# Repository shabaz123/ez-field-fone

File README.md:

# E-Z Field Fone

This repository contains a project for an intercom / field phone. The design uses discrete components throughout.  

The design includes:
- KiCad 10 Schematic and PCB files
- KiCad 10 SPICE Simulation Workbook
- Gerber files for fabrication  
- PDF schematic export and PCB screenshots for easy viewing without KiCad

# How It Works

The audio input (from on-board mic, or via a handset/earpiece jack socket) is amplified, then sent over bell wire to the remote unit. The signal on the bell wire is fed into a difference amplifier, in order to subtract the local audio. The difference output is fed into a power amplifier. The user can signal a call alert by applying a DC voltage onto the bell wire. There is an amplifier that is sensitive to DC, and the output can be used to light an indicator or sound a buzzer alert.

# Printed Circuit Board Overview

The design is split up into two separate printed circuit boards (PCBs). One PCB contains the microphone amplifier (Mic Booard) and the other contains everything else (Main Board). You'll need a mic board, and a main board, for each unit. The two boards are designed to fit into at least a couple of different enclosures. 

# Enclosures

The circuit boards will comfortably fit inside a Hammond 1559E enclosure (170 x 85 x 34 mm) along with a large 60 mm diameter (66 x 66 mm square) 8 ohm speaker such as Pui AS06608PS-R and a PP3 battery. 

If you prefer to omit the speaker and use an external handset, then a smaller Hammond 1593X (140 x 66 x 28 mm) can be used. 

If you wish to use any other enclosure, the PCB dimensions are:

Mic Board: 59 x 32.5 mm

Main Board: 59 x 55 mm

# Mic Board

The mic board uses a preamplifier designed by M. Kellett.

- **Gain:** ~45 dB  
- **Bandwidth (-3 dB):** ~100 Hz to 7 kHz (approximate)

## Schematic

## Board Connections

Two sets of soldered connections need to be made to the Mic Board; the microphone element, and the speaker. Also, an 8-pin connector is used to attach the Mic Board to the Main Board.

### Electret Mic Element

The Mic Board has a 2-pin location for soldering an electret mic element using screened cable

### Speaker

There is a 2-pin location for soldering an 8-ohm speaker

### Interfacing Connector

An 8-pin connector is used to connect a cable between the Mic Board and the Main Board. 

A ready-made JST PH 8-way "opposite direction", also known as "reverse direction" cable can be used (available from AliExpress). The opposite/reverse direction means that when laid flat, opposite sides of the connector are seen from one end to the other (this means that pin 1 of the both connectors are attached to each other, and pin 2 of both connectors are attached to each other, and so on; in contrast, a "same direction" cable has pin 1 on one connector wired to pin 8 of the other connector, and pin 2 to pin 7, and so on). 

Double-check you have the correct cable; do NOT purchase a "same direction" cable!

If you're using the larger Hammond enclosure, the cable length needs to ideally be 15cm (available from a few AliExpress stores) or alternatively 20cm (which more AliExpress stores offer). 

If you're using the smaller Hammond enclosure, a 10cm length cable should reach, but you'll need to measure it or try it out.

## 3.5 mm Audio Jack Pinout

If you wish to plug in an external mic and speaker/eaerphone, use the 3.5 mm 3-pin socket. Connections are:

- Tip: Audio Out, connect this to any earphone or headphones, or to an 8-ohm speaker
- Ring: Microphone, connect this to an electret mic element (the Mic Board PCB supplies a low voltage to power the element)
- Shield: Ground

## PCB Top

## PCB Underside

Note that one wire link needs to be made on the underside; it is labeled on the board.

## PCB Render

## Enclosure Cutouts

The Mic Board requires the following holes to be drilled in the enclosure:

- DC barrel socket
- Rotary switch (4-position, for Off/Standby/On/Call)
- Power ON LED indicator
- 3.5 mm audio socket (for external mic and external earphone/speaker)
- Hole for electret mic element

---

# Main Board

The main board includes a 280mW audio amplifier designed by M. Kellett. 

## Schematic

Note: Resistor R35 is specified to be 630 ohm, this is a hard-to-find value, it may be replaced by 620 ohm in series with 10 ohm (on the PCB, solder 620 ohm and 10 ohm vertically, and connect them at the top with solder).

## Board Connections

The only off-board connection from the Main Board is the 8-way connection that interfaces to the Mic Board. See the Mic Board notes earlier, for an explanation of the required cable (8-way JST PH cable, "opposite/reverse direction", i.e. identical pin mapping, pin 1 to pin 1, and pin 2 to pin 2, and so on).

## PCB Top

## PCB Underside

Note that there are two wire links that need to be soldered on the board underside. The connections are labeled A and B on the circuit board (connect A to A, and connect B to B).

## PCB Render

## Enclosure Cutouts

The Main Board requires the following holes to be drilled in the enclosure:

- An approximately 9 x 7.5 mm rectangular hole for a 3.81 mm pitch 2-way plug-in terminal block, used for attaching bell wire
- Two approximately 6 mm diameter holes, one for the mute button, and one for the recessed line termination button (the bell wire needs terminating at one end)
- 7.5 mm dia hole for the volume control potentiometer
- Hole for the call alert LED indicator
- Hole for an audio buzzer (if a buzzer is fitted) for audible call alerts

---

## Notes

All components are easy to source. 

For the input power, use a 9V PP3 battery, or use the 9V DC barrel socket (center positive).

The potentiometer can be ALPS RK097 series (available from AliExpress), it has pins at 2.5 mm pitch, and a body width of 10 mm.

The rotary switch is type RS1010 4-way (available from AliExpress)

The push switches can be either PS-12E05, or PN12 series by CK/Littelfuse

For the trimmer resistor, RM065 series will fit the PCB

The line connector (for attaching the bell wire) is a 2-way 3.81 mm pitch terminal block, there are many generic options. One example is WJ15EDGRC-3.81-02P-14-00A (which mates with part code WJ15EDGK-3.81-02P-14-00A

---

# Parts Lists

## Mic Board Parts List

| Reference  | Qty | Value             | Description                             |
| ---------- | --- | ----------------- | --------------------------------------- |
| C1         | 1   | 47u               | Electrolytic Capacitor 5mm dia          |
| C2,C3,C5   | 3   | 22u               | Electrolytic Capacitor 5mm dia          |
| C4         | 1   | 100n              | Ceramic Capacitor 5mm pitch             |
| C6         | 1   | 220p              | Ceramic Capacitor 5mm pitch             |
| C7         | 1   | 2.2n              | Ceramic Capacitor 5mm pitch             |
| D1         | 1   | 1N4148            | Small Signal Diode                      |
| D3         | 1   | LED_ON            | LED 3mm dia                             |
| J1         | 1   | ELECTRET_MIC      | Electret Mic Element                    |
| J2         | 1   | HANDSET           | SJ1-3525N 3.5mm jack CUI                |
| J3         | 1   | DC-Socket         | 2.1/5.5mm DC Jack Socket                |
| J4         | 1   | PP3 BATT          | Battery Clip PP3                        |
| J5         | 1   | SPEAKER           | AS06608PS-R 8-ohm  60mm dia (66 x 66mm) |
| J6         | 1   | B8B-PH-K-S        | JST PH Header 8-way Vertical            |
| Q1,Q3      | 2   | BC549             | NPN TO-92 Low Noise BJT                 |
| Q2         | 1   | BC559             | PNP TO-92 Low Noise BJT                 |
| Q4         | 1   | BC547             | NPN TO-92 BJT                           |
| Q5         | 1   | BS250P            | P-ch MOSFET TO-92                       |
| R1,R14,R17 | 3   | 1k                | Resistor 1/8W or 1/4W                   |
| R2         | 1   | 10k               | Resistor 1/8W or 1/4W                   |
| R3         | 1   | 91k               | Resistor 1/8W or 1/4W                   |
| R4         | 1   | 180k              | Resistor 1/8W or 1/4W                   |
| R5         | 1   | 56k               | Resistor 1/8W or 1/4W                   |
| R6         | 1   | 82R               | Resistor 1/8W or 1/4W                   |
| R7         | 1   | 560R              | Resistor 1/8W or 1/4W                   |
| R8         | 1   | 5.6k              | Resistor 1/8W or 1/4W                   |
| R9         | 1   | 2.7k              | Resistor 1/8W or 1/4W                   |
| R10        | 1   | 16k               | Resistor 1/8W or 1/4W                   |
| R11        | 1   | 4.7k              | Resistor 1/8W or 1/4W                   |
| R12,R13    | 2   | 3.9k              | Resistor 1/8W or 1/4W                   |
| R15        | 1   | 22k               | Resistor 1/8W or 1/4W                   |
| R16        | 1   | 1M                | Resistor 1/8W or 1/4W                   |
| SW1        | 1   | RS1010-2Pole-4Pos | 2P4T Rotary Switch                      |
| n/a        | 1   | JST PH 15cm Cable | 8way Opposite/Reverse Direction cable   |
| n/a        | 1   | Knob 6mm Knurled  | 15mm dia outer, flower inner hole 6mm   |

## Main Board Parts List
| Reference                     | Qty | Value             | Description                           |
| ----------------------------- | --- | ----------------- | ------------------------------------- |
| C1,C5,C9,C10,C13              | 5   | 10u               | Electrolytic Capacitor 5mm dia        |
| C2,C8                         | 2   | 22u               | Electrolytic Capacitor 5mm dia        |
| C3,C4                         | 2   | 1u                | Ceramic Capacitor 5mm pitch           |
| C6                            | 1   | 10n               | Ceramic Capacitor 5mm pitch           |
| C7                            | 1   | 470p              | Ceramic Capacitor 5mm pitch           |
| C11                           | 1   | 47u               | Electrolytic Capacitor 5mm dia        |
| C12                           | 1   | 220n              | Ceramic Capacitor 5mm pitch           |
| C14                           | 1   | 270p              | Ceramic Capacitor 2.5mm pitch         |
| C15                           | 1   | 100u              | Electrolytic Capacitor 6.3mm dia      |
| C16                           | 1   | 470u              | Electrolytic Capacitor 8mm dia        |
| D1,D3,D4,D5                   | 4   | 1N4148            | Small Signal Diode                    |
| D2                            | 1   | LED_ALERT         | LED 3mm dia                           |
| J1                            | 1   | Term Block 3.81mm | 2-way WJ15EDGRC-3.81-02P-14-00A       |
| J2                            | 1   | B8B-PH-K-S        | JST PH Header 8-way Vertical          |
| J3                            | 1   | EXT_BUZZER        | 9V Buzzer (optional)                  |
| Q1,Q3,Q5,Q6,Q8,Q9,Q11,Q12,Q15 | 9   | BC547             | NPN TO-92 BJT                         |
| Q2,Q4,Q13,Q14                 | 4   | BC557             | PNP TO-92 BJT                         |
| Q7                            | 1   | J113              | N-ch JFET TO-92                       |
| Q10                           | 1   | BS250P            | P-ch MOSFET TO-92                     |
| Q16                           | 1   | BC337-25          | NPN TO-92 Power BJT                   |
| Q17                           | 1   | BC327-25          | PNP TO-92 Power BJT                   |
| R1                            | 1   | 22k               | RM065 Trimmer Potentiometer           |
| R2,R3,R4,R5,R19,R38,R39,R42   | 8   | 1k                | Resistor 1/8W or 1/4W                 |
| R6,R18,R21,R26,R30,R34        | 6   | 10k               | Resistor 1/8W or 1/4W                 |
| R7,R8,R22,R23,R43             | 5   | 22k               | Resistor 1/8W or 1/4W                 |
| R9,R12                        | 2   | 220k              | Resistor 1/8W or 1/4W                 |
| R10,R11,R13,R15               | 4   | 470R              | Resistor 1/8W or 1/4W                 |
| R14                           | 1   | 1M                | Resistor 1/8W or 1/4W                 |
| R16                           | 1   | 100R              | Resistor 1/8W or 1/4W                 |
| R17                           | 1   | 3.3k              | Resistor 1/8W or 1/4W                 |
| R20,R29,R31,R33               | 4   | 33k               | Resistor 1/8W or 1/4W                 |
| R24                           | 1   | 2.7k              | Resistor 1/8W or 1/4W                 |
| R25,R27                       | 2   | 47k               | Resistor 1/8W or 1/4W                 |
| R28                           | 1   | 22k               | Resistor 1/8W or 1/4W                 |
| R32                           | 1   | 43k               | Resistor 1/8W or 1/4W                 |
| R35                           | 1   | 630R (620R+10R)   | Resistor 1/8W or 1/4W                 |
| R36                           | 1   | 1.5k              | Resistor 1/8W or 1/4W                 |
| R37                           | 1   | 100k              | Resistor 1/8W or 1/4W                 |
| R40                           | 1   | 27k               | Resistor 1/8W or 1/4W                 |
| R41                           | 1   | 2k                | Resistor 1/8W or 1/4W                 |
| R44                           | 1   | 150R              | Resistor 1/8W or 1/4W                 |
| R45,R46                       | 2   | 2.2R              | Resistor 1/4W                         |
| SW1                           | 1   | PS-12E05          | SPDT Switch Latching PN12             |
| SW2                           | 1   | PS-12E05          | SPDT Switch Latching PN12             |
| n/a                           | 1   | Plug 3.81mm       | 2-way WJ15EDGK-3.81-02P-14-00A        |
| n/a                           | 1   | Knob 6mm Knurled  | 15mm dia outer, flower inner hole 6mm |

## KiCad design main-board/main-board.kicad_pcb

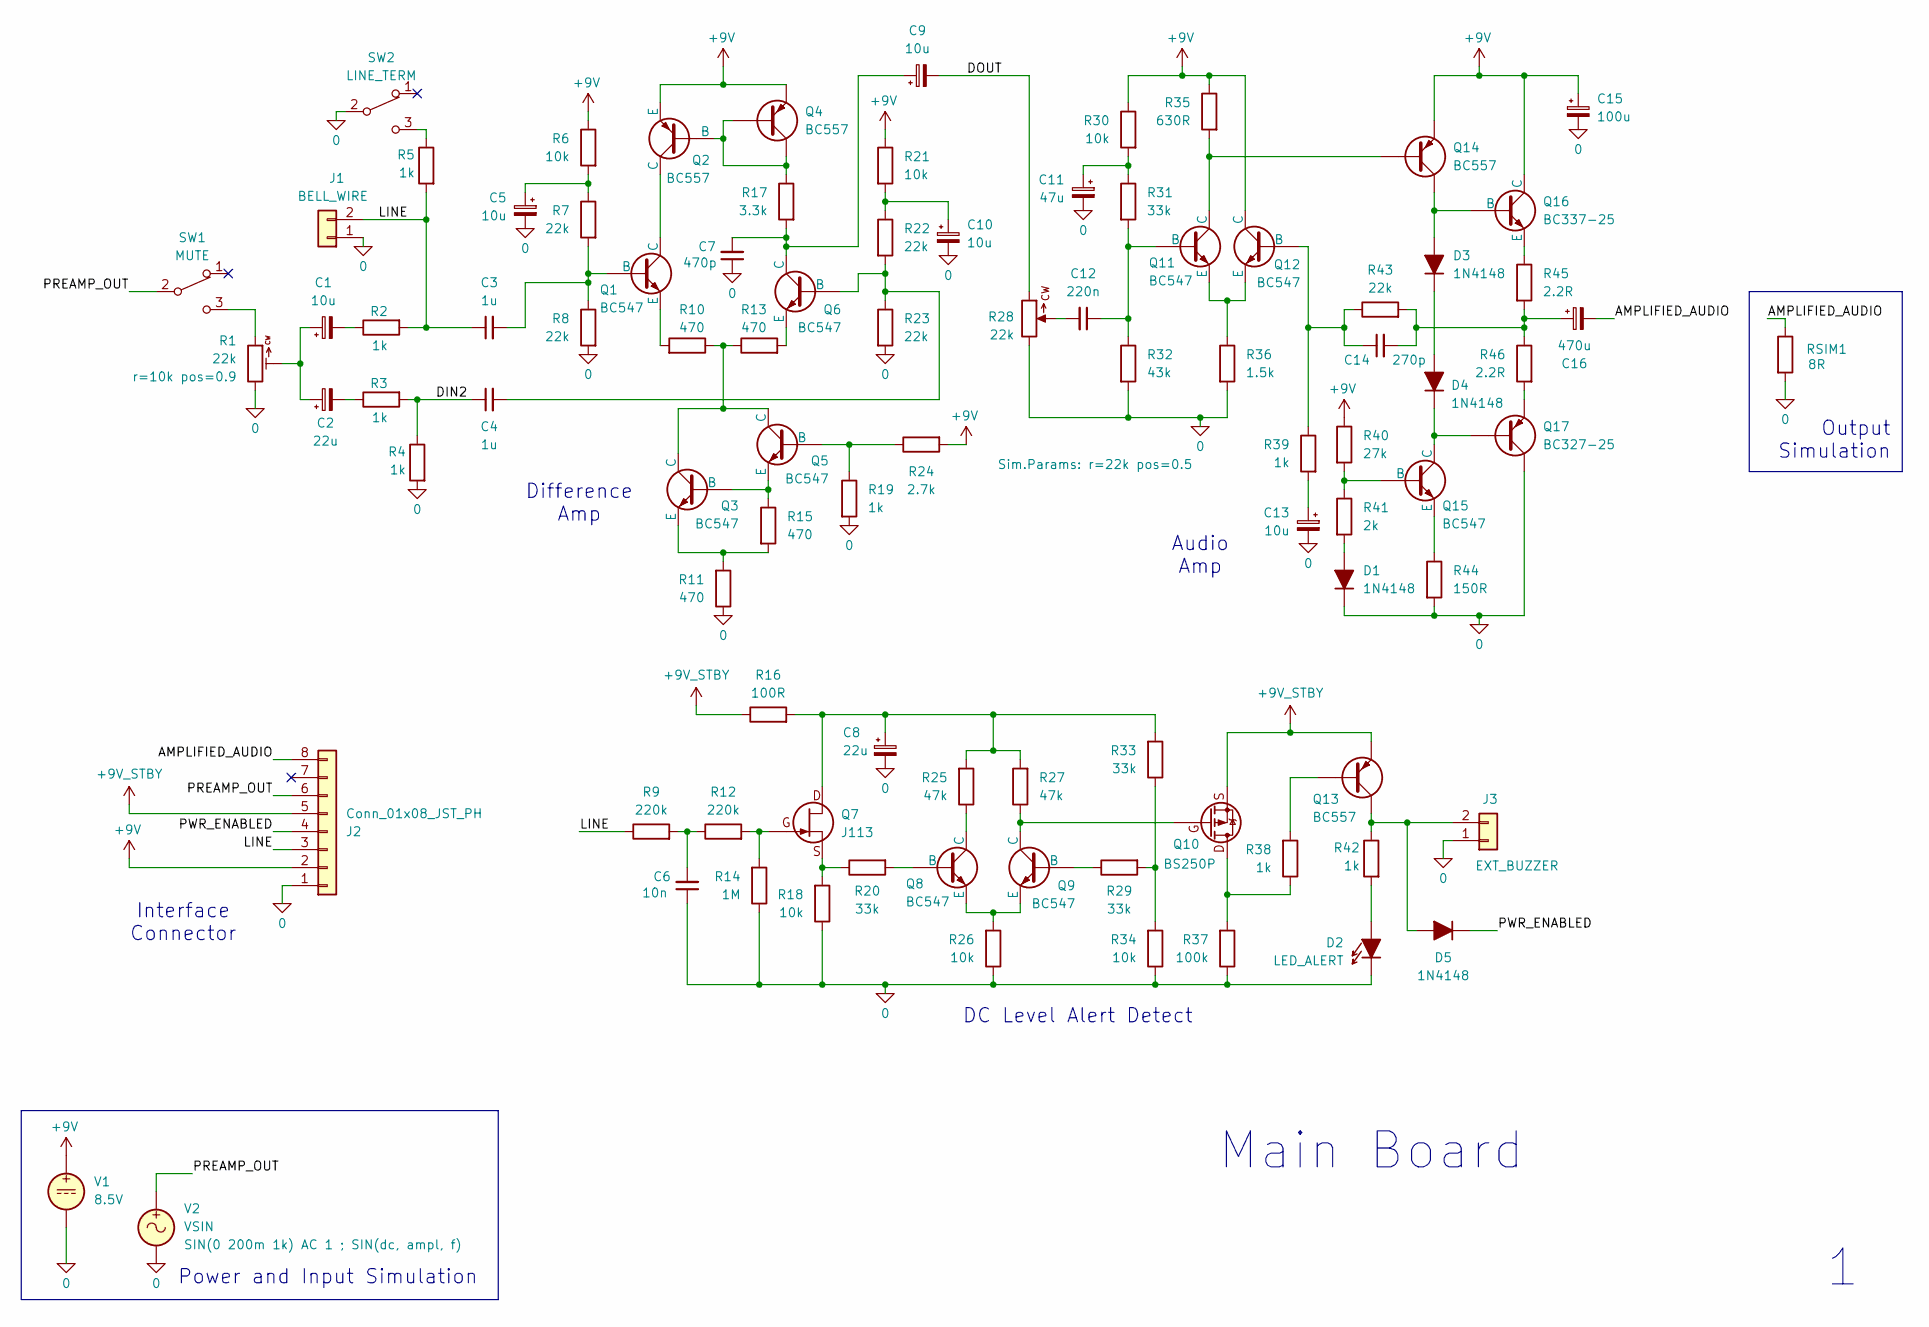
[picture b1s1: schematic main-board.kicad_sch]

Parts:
C1, C5, C9, C10, C13: 10u; CP_Radial_D5.0mm_P2.50mm
C2, C8: 22u; CP_Radial_D5.0mm_P2.50mm
C3, C4: 1u; C_Disc_T3.0mm_P5.0
C6: 10n; C_Disc_T3.0mm_P5.0
C7: 470p; C_Disc_T3.0mm_P5.0
C11: 47u; CP_Radial_D5.0mm_P2.50mm
C12: 220n; C_Disc_T3.0mm_P5.0
C14: 270p; C_Disc_T2.5mm_P2.5
C15: 100u; CP_Radial_D6.3mm_P2.50mm
C16: 470u; CP_Radial_D8mm_P3.5mm
D1, D3, D4, D5: 1N4148; D_DO-35_P2.54mm_Vertical_CathodeUp
D2: LED_ALERT; LED_3mm
J1: BELL_WIRE; TerminalBlock_RightAngle-2way-3.81mm
J2: Conn_01x08_JST_PH; JST_PH_Vertical_8way
J3: EXT_BUZZER; PinHeader_1x02_P2.54mm_Vertical
Q1, Q3, Q5, Q8, Q9, Q11, Q12, Q15: BC547; BJT_NPN_BC547_Compact
Q2, Q4, Q13: BC557; BJT_PNP_BC557_Compact
Q6: BC547; BJT_PNP_BC557_Compact
Q7: J113; J113_NCH_JFET_Compact
Q10: BS250P; MOSFET_BS250P_Compact
Q14: BC557; BJT_PNP_BC557_Compact2
Q16: BC337-25; BJT_NPN_BC547_Compact
Q17: BC327-25; BJT_PNP_BC557_Compact
R1: 22k; Potentiometer_Trimmer_RM065
R2, R3, R4, R5, R19, R38, R39, R42: 1k; R_Axial_L6.3mm_D2.5mm_P2.54mm_Vertical
R6, R18, R21, R26, R30, R34: 10k; R_Axial_L6.3mm_D2.5mm_P2.54mm_Vertical
R7, R8, R22, R23, R43: 22k; R_Axial_L6.3mm_D2.5mm_P2.54mm_Vertical
R9, R12: 220k; R_Axial_L6.3mm_D2.5mm_P2.54mm_Vertical
R10, R11, R13, R15: 470; R_Axial_L6.3mm_D2.5mm_P2.54mm_Vertical
R14: 1M; R_Axial_L6.3mm_D2.5mm_P2.54mm_Vertical
R16: 100R; R_Axial_L6.3mm_D2.5mm_P2.54mm_Vertical
R17: 3.3k; R_Axial_L6.3mm_D2.5mm_P2.54mm_Vertical
R20, R29, R31, R33: 33k; R_Axial_L6.3mm_D2.5mm_P2.54mm_Vertical
R24: 2.7k; R_Axial_L6.3mm_D2.5mm_P2.54mm_Vertical
R25, R27: 47k; R_Axial_L6.3mm_D2.5mm_P2.54mm_Vertical
R28: 22k; Potentiometer_RD701F
R32: 43k; R_Axial_L6.3mm_D2.5mm_P2.54mm_Vertical
R35: 630R; R_Axial_L6.3mm_D2.5mm_P2.54mm_Vertical
R36: 1.5k; R_Axial_L6.3mm_D2.5mm_P2.54mm_Vertical
R37: 100k; R_Axial_L6.3mm_D2.5mm_P2.54mm_Vertical
R40: 27k; R_Axial_L6.3mm_D2.5mm_P2.54mm_Vertical
R41: 2k; R_Axial_L6.3mm_D2.5mm_P2.54mm_Vertical
R44: 150R; R_Axial_L6.3mm_D2.5mm_P2.54mm_Vertical
R45, R46: 2.2R; R_Axial_L6.3mm_D2.5mm_P2.54mm_Vertical
RSIM1: 8R; R_Axial_L6.3mm_D2.5mm_P10.16mm_Horiz
SW1: MUTE; PS-12E05
SW2: LINE_TERM; PS-12E05
V1: 8.5V
V2: VSIN

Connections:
0: C5.2, C6.1, C7.1, C8.2, C10.2, C11.2, C13.2, C15.2, D1.1 (K), D2.1 (K), J1.1, J2.1, J3.1, Q17.1 (C), R1.1, R4.2, R8.2, R11.1, R14.1, R18.1, R19.2, R23.2, R26.1, R28.1, R32.2, R34.1, R36.2, R37.1, R44.2, RSIM1.2, SW2.2 (B), V1.2, V2.2
+9V: C15.1, J2.2, Q2.3 (E), Q4.3 (E), Q12.1 (C), Q14.3 (E), Q16.1 (C), R6.1, R21.1, R24.2, R30.1, R35.1, R40.1, V1.1
+9V_STBY: J2.5, Q10.1 (S), Q13.3 (E), R16.1
/AMPLIFIED_AUDIO: C16.2, J2.8, RSIM1.1
/DIN2: C4.1, R3.2, R4.1
/DOUT: C9.2, R28.3
/LINE: C3.1, J1.2, J2.3, R2.2, R5.2, R9.1
/PREAMP_OUT: J2.6, SW1.2 (B), V2.1
/PWR_ENABLED: D5.1 (K), J2.4
unnamed: C1.1, C2.1, R1.2
unnamed: C1.2, R2.1
unnamed: C2.2, R3.1
unnamed: C5.1, R6.2, R7.1
unnamed: C6.2, R9.2, R12.1
unnamed: C10.1, R21.2, R22.1
unnamed: C11.1, R30.2, R31.1
unnamed: C12.2, R28.2
unnamed: C13.1, R39.2
unnamed: C14.2, C16.1, R43.2, R45.2, R46.1
unnamed: D1.2 (A), R41.2
unnamed: D2.2 (A), R42.2
unnamed: D3.2 (A), Q14.1 (C), Q16.2 (B)
unnamed: D3.1 (K), D4.2 (A)
unnamed: D4.1 (K), Q15.1 (C), Q17.2 (B)
unnamed: D5.2 (A), J3.2, Q13.1 (C), R42.1
unnamed: C3.2, Q1.2 (B), R7.2, R8.1
unnamed: Q1.1 (C), Q2.1 (C)
unnamed: Q1.3 (E), R10.2
unnamed: Q2.2 (B), Q4.1 (C), Q4.2 (B), R17.1
unnamed: Q3.2 (B), Q5.3 (E), R15.1
unnamed: Q3.1 (C), Q5.1 (C), R10.1, R13.1
unnamed: Q3.3 (E), R11.2, R15.2
unnamed: Q5.2 (B), R19.1, R24.1
unnamed: C4.2, Q6.2 (B), R22.2, R23.1
unnamed: C7.2, C9.1, Q6.1 (C), R17.2
unnamed: Q6.3 (E), R13.2
unnamed: C8.1, Q7.1 (D), R16.2, R25.2, R27.2, R33.2
unnamed: Q7.3 (G), R12.2, R14.2
unnamed: Q7.2 (S), R18.2, R20.1
unnamed: Q8.2 (B), R20.2
unnamed: Q8.1 (C), R25.1
unnamed: Q8.3 (E), Q9.3 (E), R26.2
unnamed: Q9.2 (B), R29.1
unnamed: Q10.3 (D), R37.2, R38.1
unnamed: Q9.1 (C), Q10.2 (G), R27.1
unnamed: C12.1, Q11.2 (B), R31.2, R32.1
unnamed: Q11.1 (C), Q14.2 (B), R35.2
unnamed: Q11.3 (E), Q12.3 (E), R36.1
unnamed: C14.1, Q12.2 (B), R39.1, R43.1
unnamed: Q13.2 (B), R38.2
unnamed: Q15.2 (B), R40.2, R41.1
unnamed: Q15.3 (E), R44.1
unnamed: Q16.3 (E), R45.1
unnamed: Q17.3 (E), R46.2
unnamed: R29.2, R33.1, R34.2
unnamed: R1.3, SW1.3 (C)
unnamed: R5.1, SW2.3 (C)

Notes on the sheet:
Power and Input Simulation
Output Simulation
DC Level Alert Detect
Interface Connector
Difference Amp
Audio Amp
Main Board

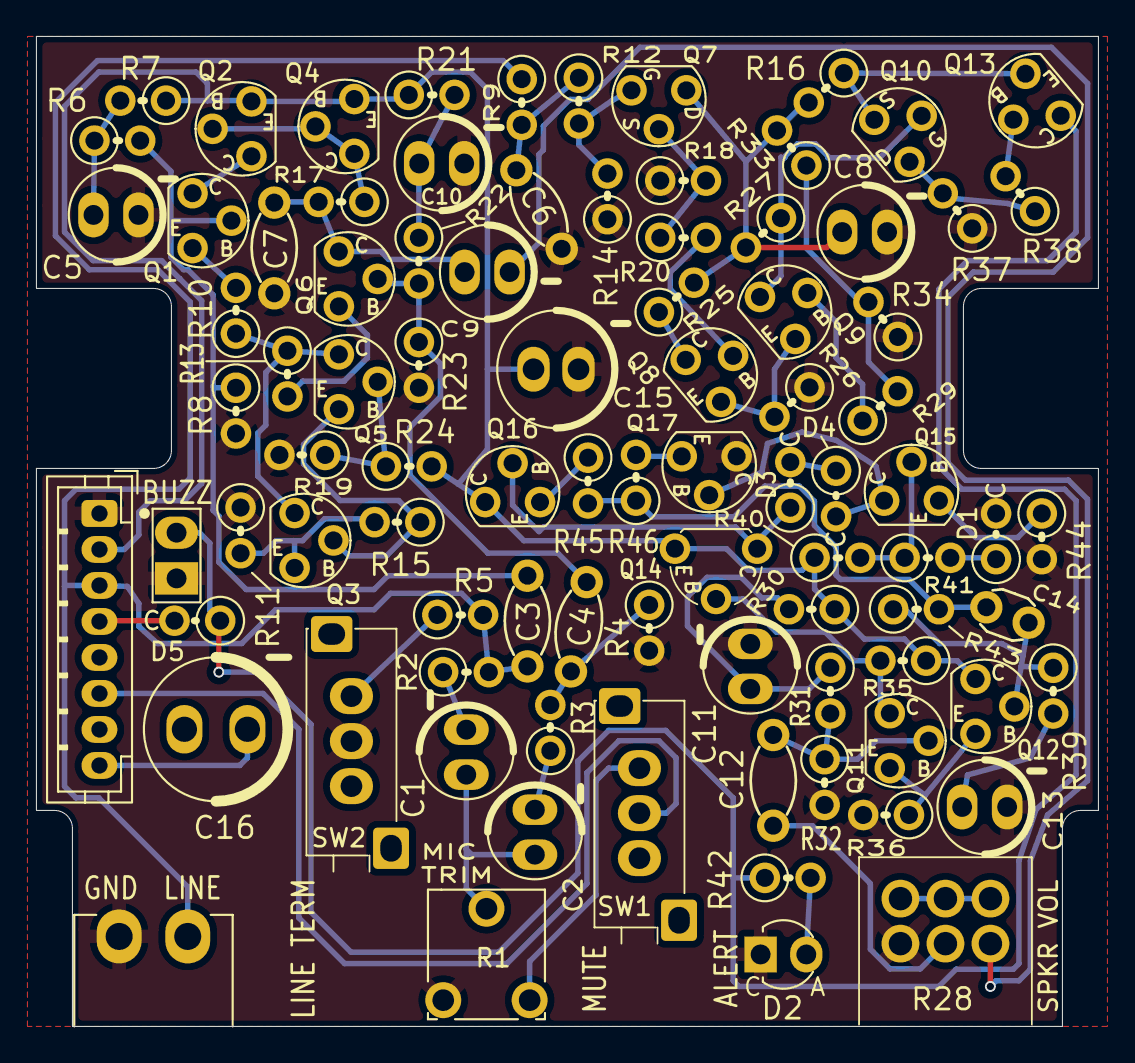
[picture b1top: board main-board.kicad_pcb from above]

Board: 2 copper layers, 59.0 x 55.0 mm, 89 parts (0 on the bottom side), 57 nets.

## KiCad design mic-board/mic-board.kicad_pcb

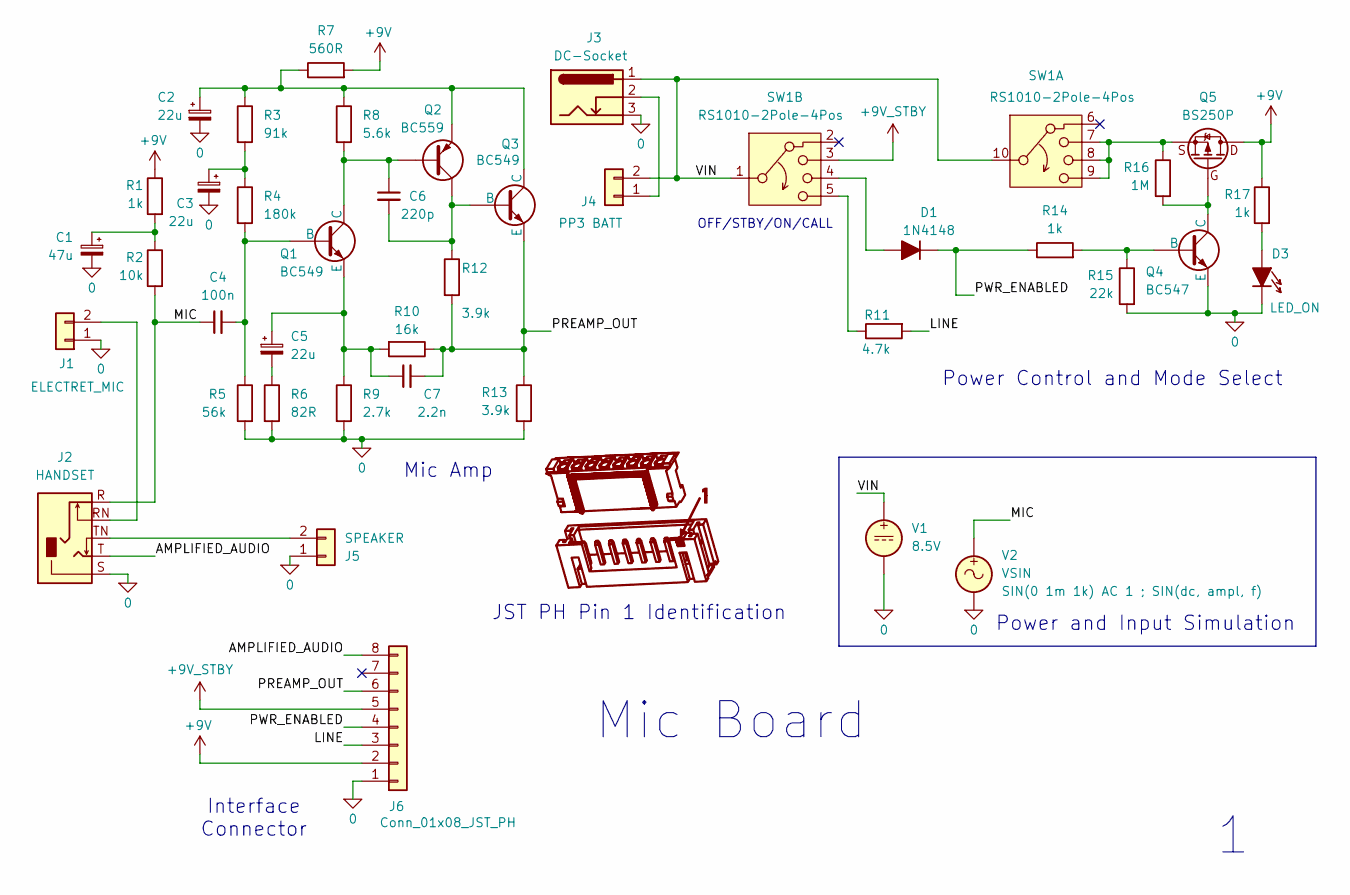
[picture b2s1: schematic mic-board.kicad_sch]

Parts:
C1: 47u; CP_Radial_D5.0mm_P2.50mm
C2, C3, C5: 22u; CP_Radial_D5.0mm_P2.50mm
C4: 100n; C_Disc_T3.0mm_P5.0
C6: 220p; C_Disc_T3.0mm_P5.0
C7: 2.2n; C_Disc_T3.0mm_P5.0
D1: 1N4148; D_DO-35_P2.54mm_Vertical_CathodeUp
D3: LED_ON; LED_3mm
J1: ELECTRET_MIC; PinHeader_1x02_P2.54mm_Vertical
J2: HANDSET; Jack_3.5mm_CUI_SJ1-3525N_Horizontal2
J3: DC-Socket; DC-Jack-10-extra-reduced-silk
J4: PP3 BATT; PinHeader_1x02_P2.54mm_Vertical
J5: SPEAKER; PinHeader_1x02_P2.54mm_Vertical
J6: Conn_01x08_JST_PH; JST_PH_Vertical_8way
Q1, Q3: BC549; BJT_NPN_BC547_Compact
Q2: BC559; BJT_PNP_BC557_Compact
Q4: BC547; BJT_NPN_BC547_Compact
Q5: BS250P; MOSFET_BS250P_Compact
R1, R14, R17: 1k; R_Axial_L6.3mm_D2.5mm_P2.54mm_Vertical
R2: 10k; R_Axial_L6.3mm_D2.5mm_P2.54mm_Vertical
R3: 91k; R_Axial_L6.3mm_D2.5mm_P2.54mm_Vertical
R4: 180k; R_Axial_L6.3mm_D2.5mm_P2.54mm_Vertical
R5: 56k; R_Axial_L6.3mm_D2.5mm_P2.54mm_Vertical
R6: 82R; R_Axial_L6.3mm_D2.5mm_P2.54mm_Vertical
R7: 560R; R_Axial_L6.3mm_D2.5mm_P2.54mm_Vertical
R8: 5.6k; R_Axial_L6.3mm_D2.5mm_P2.54mm_Vertical
R9: 2.7k; R_Axial_L6.3mm_D2.5mm_P2.54mm_Vertical
R10: 16k; R_Axial_L6.3mm_D2.5mm_P2.54mm_Vertical
R11: 4.7k; R_Axial_L6.3mm_D2.5mm_P2.54mm_Vertical
R12, R13: 3.9k; R_Axial_L6.3mm_D2.5mm_P2.54mm_Vertical
R15: 22k; R_Axial_L6.3mm_D2.5mm_P2.54mm_Vertical
R16: 1M; R_Axial_L6.3mm_D2.5mm_P2.54mm_Vertical
SW1: RS1010-2Pole-4Pos; RS1010
V1: 8.5V
V2: VSIN

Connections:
0: C1.2, C2.2, C3.2, D3.1 (K), J1.1, J2.S, J3.3, J5.1, J6.1, Q4.3 (E), R5.2, R6.2, R9.2, R13.2, R15.2, V1.2, V2.2
+9V: J6.2, Q5.3 (D), R1.1, R7.2, R17.1
+9V_STBY: J6.5, SW1.3
/AMPLIFIED_AUDIO: J2.T, J6.8
/LINE: J6.3, R11.2
/MIC: C4.1, J2.R, R2.2, V2.1
/PREAMP_OUT: C7.2, J6.6, Q3.3 (E), R10.1, R12.2, R13.1
/PWR_ENABLED: D1.1 (K), J6.4, R14.1
/VIN: J3.1, J4.2, SW1.1, SW1.10, V1.1
unnamed: C1.1, R1.2, R2.1
unnamed: C3.1, R3.2, R4.1
unnamed: C5.2, R6.1
unnamed: D1.2 (A), SW1.4
unnamed: D3.2 (A), R17.2
unnamed: J1.2, J2.RN
unnamed: J3.2, J4.1
unnamed: J2.TN, J5.2
unnamed: C4.2, Q1.2 (B), R4.2, R5.1
unnamed: C6.1, Q1.1 (C), Q2.2 (B), R8.2
unnamed: C5.1, C7.1, Q1.3 (E), R9.1, R10.2
unnamed: C6.2, Q2.1 (C), Q3.2 (B), R12.1
unnamed: C2.1, Q2.3 (E), Q3.1 (C), R3.1, R7.1, R8.1
unnamed: Q4.2 (B), R14.2, R15.1
unnamed: Q4.1 (C), Q5.2 (G), R16.2
unnamed: Q5.1 (S), R16.1, SW1.7, SW1.8, SW1.9
unnamed: R11.1, SW1.5

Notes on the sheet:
Power and Input Simulation
OFF/STBY/ON/CALL
JST PH Pin 1 Identification
Interface Connector
Mic Amp
Power Control and Mode Select
Mic Board

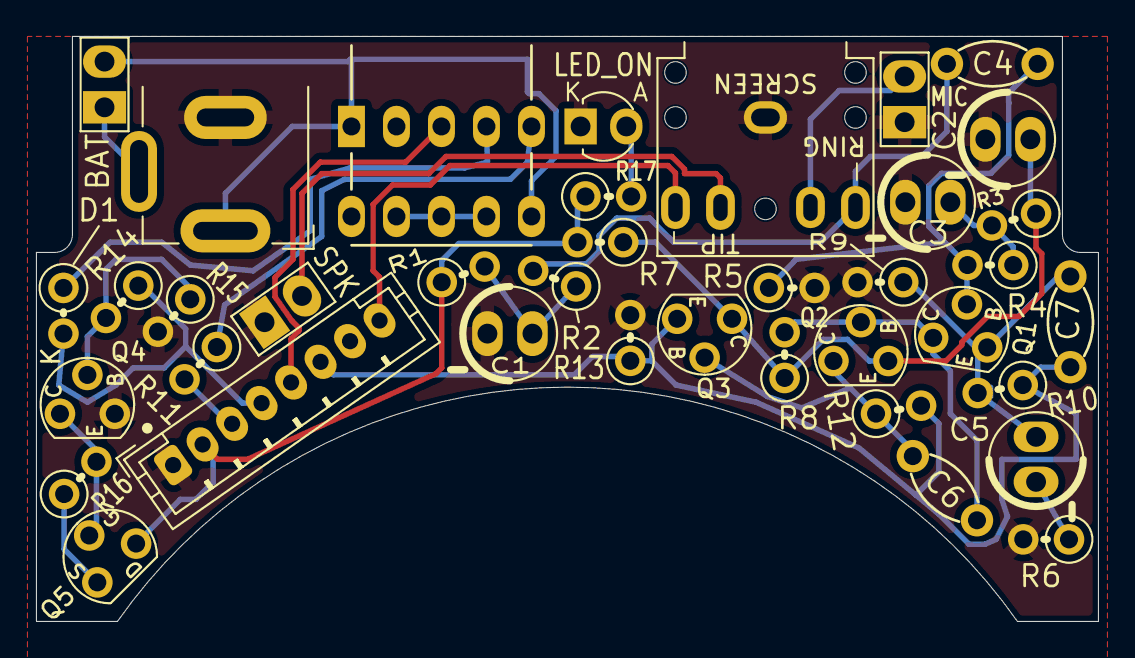
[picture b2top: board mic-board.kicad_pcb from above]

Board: 2 copper layers, 59.0 x 32.5 mm, 38 parts (0 on the bottom side), 26 nets.

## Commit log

2026-04-26 Add enclosure cutouts section to README
    Added details about enclosure cutouts required for the Main Board.
2026-04-27 Add parts lists for Mic and Main Boards
    Added detailed parts lists for Mic Board and Main Board.
2026-04-27 Update R35 resistor description in README
2026-04-27 Update resistor R35 replacement instructions
    Clarified instructions for replacing resistor R35 in the schematic section.
2026-04-27 Clarify cable direction terminology in README
